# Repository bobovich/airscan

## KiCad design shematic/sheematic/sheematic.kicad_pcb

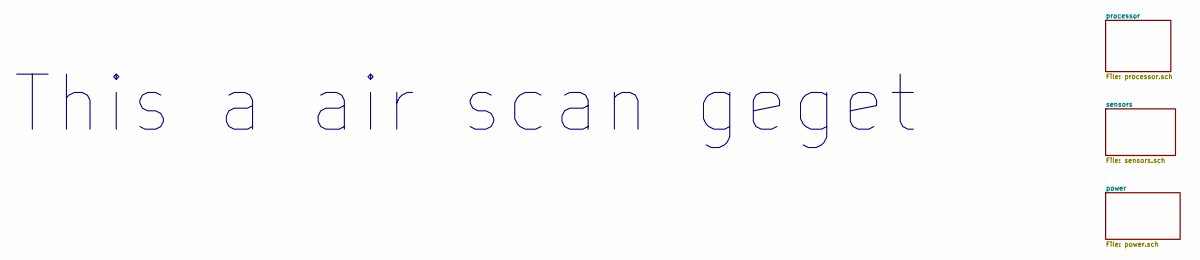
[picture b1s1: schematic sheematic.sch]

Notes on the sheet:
This a air scan geget

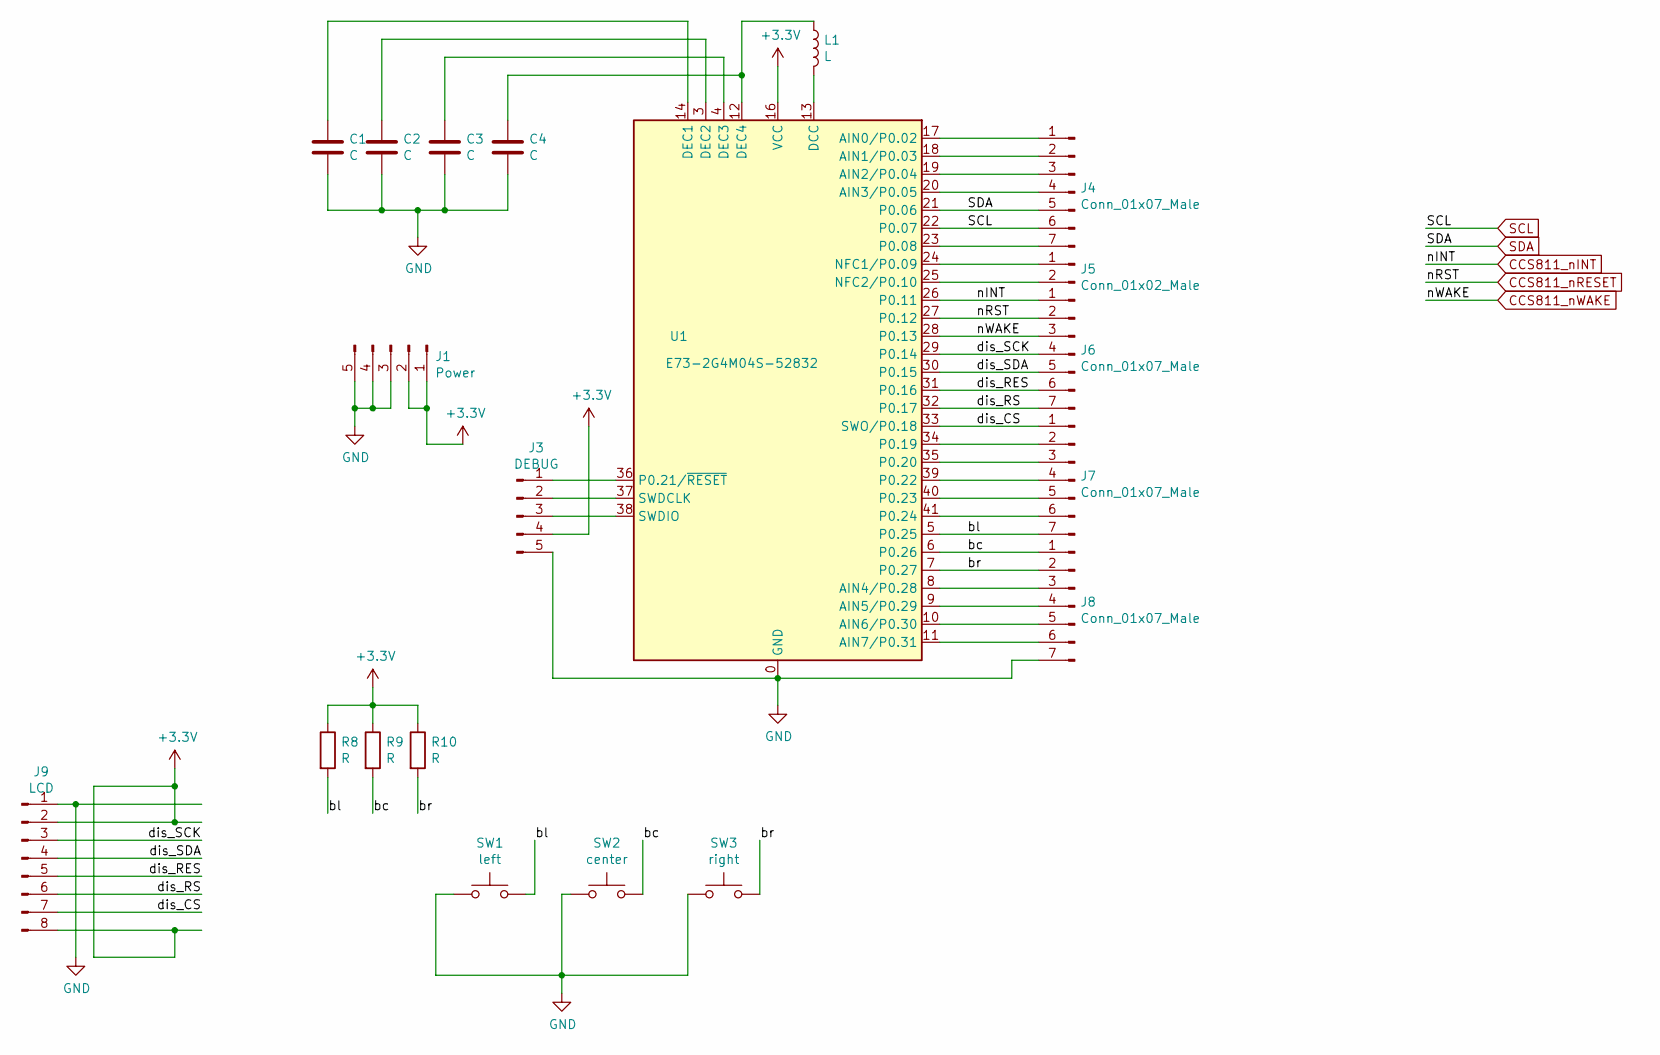
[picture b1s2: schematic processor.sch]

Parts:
C1, C2, C3, C4: C; C_0603_1608Metric_Pad1.08x0.95mm_HandSolder
J1: Power; PinHeader_1x05_P2.54mm_Vertical
J3: DEBUG; PinHeader_1x05_P2.54mm_Vertical
J4, J6, J7, J8: Conn_01x07_Male; PinHeader_1x07_P2.54mm_Vertical
J5: Conn_01x02_Male; PinHeader_1x02_P2.54mm_Vertical
J9: LCD; PinHeader_1x08_P2.54mm_Vertical
L1: L; L_0805_2012Metric_Pad1.15x1.40mm_HandSolder
R8, R9, R10: R; R_0603_1608Metric_Pad1.05x0.95mm_HandSolder
SW1: left; SW_PUSH_6mm
SW2: center; SW_PUSH_6mm
SW3: right; SW_PUSH_6mm
U1: E73-2G4M04S-52832; E73-2G4M04S

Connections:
+3V3: J1.1, J1.2, J3.4, J9.2, J9.8, R8.1, R9.1, R10.1, U1.16 (VCC); also elsewhere on the board
/processor/bc: J8.1, R9.2, SW2.2, U1.6 (P0.26)
/processor/bl: J7.7, R8.2, SW1.2, U1.5 (P0.25)
/processor/br: J8.2, R10.2, SW3.2, U1.7 (P0.27)
/processor/dis_CS: J7.1, J9.7, U1.33 (SWO/P0.18)
/processor/dis_RES: J6.6, J9.5, U1.31 (P0.16)
/processor/dis_RS: J6.7, J9.6, U1.32 (P0.17)
/processor/dis_SCK: J6.4, J9.3, U1.29 (P0.14)
/processor/dis_SDA: J6.5, J9.4, U1.30 (P0.15)
CCS811_nINT: J6.1, U1.26 (P0.11); also elsewhere on the board
CCS811_nRESET: J6.2, U1.27 (P0.12); also elsewhere on the board
CCS811_nWAKE: J6.3, U1.28 (P0.13); also elsewhere on the board
GND: C1.2, C2.2, C3.2, C4.2, J1.3, J1.4, J1.5, J3.5, J8.7, J9.1, SW1.1, SW2.1, SW3.1, U1.0 (GND), U1.1 (GND), U1.2 (GND), U1.15 (GND), U1.42 (GND), U1.43 (GND); also elsewhere on the board
unnamed: C1.1, U1.14 (DEC1)
unnamed: C2.1, U1.3 (DEC2)
unnamed: C3.1, U1.4 (DEC3)
unnamed: C4.1, L1.1, U1.12 (DEC4)
unnamed: J3.1, U1.36 (P0.21/~RESET)
unnamed: J3.2, U1.37 (SWDCLK)
unnamed: J3.3, U1.38 (SWDIO)
unnamed: J4.1, U1.17 (AIN0/P0.02)
unnamed: J4.2, U1.18 (AIN1/P0.03)
unnamed: J4.3, U1.19 (AIN2/P0.04)
unnamed: J4.4, U1.20 (AIN3/P0.05)
unnamed: J4.7, U1.23 (P0.08)
unnamed: J5.1, U1.24 (NFC1/P0.09)
unnamed: J5.2, U1.25 (NFC2/P0.10)
unnamed: J7.2, U1.34 (P0.19)
unnamed: J7.3, U1.35 (P0.20)
unnamed: J7.4, U1.39 (P0.22)
unnamed: J7.5, U1.40 (P0.23)
unnamed: J7.6, U1.41 (P0.24)
unnamed: J8.3, U1.8 (AIN4/P0.28)
unnamed: J8.4, U1.9 (AIN5/P0.29)
unnamed: J8.5, U1.10 (AIN6/P0.30)
unnamed: J8.6, U1.11 (AIN7/P0.31)
unnamed: L1.2, U1.13 (DCC)
SCL: J4.6, U1.22 (P0.07); also elsewhere on the board
SDA: J4.5, U1.21 (P0.06); also elsewhere on the board

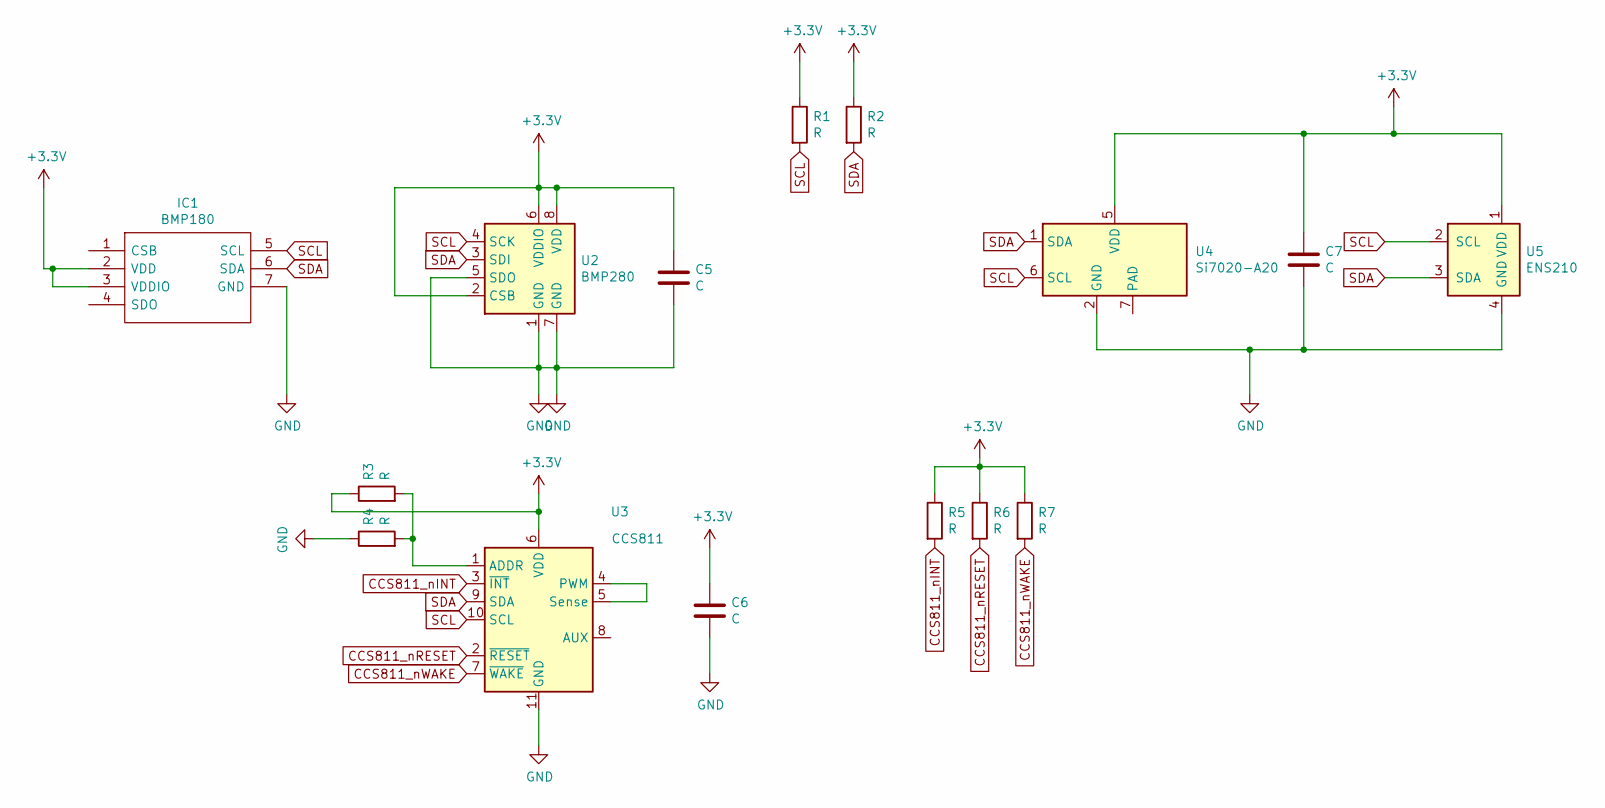
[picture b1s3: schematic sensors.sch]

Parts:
C5, C6, C7: C; C_0603_1608Metric_Pad1.08x0.95mm_HandSolder
IC1: BMP180; Manufacturer_Part_Number BMP180; Mouser Part Number 262-BMP180
R1, R2, R3, R4, R5, R6, R7: R; R_0603_1608Metric_Pad1.05x0.95mm_HandSolder
U2: BMP280; Bosch_LGA-8_2x2.5mm_P0.65mm_ClockwisePinNumbering
U3: CCS811; AMS_LGA-10-1EP_2.7x4mm_P0.6mm
U4: Si7020-A20; DFN-6-1EP_3x3mm_P1mm_EP1.5x2.4mm
U5: ENS210; AMS_QFN-4-1EP_2x2mm_P0.95mm_EP0.7x1.6mm

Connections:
+3V3: C5.1, C6.1, C7.1, IC1.2 (VDD), IC1.3 (VDDIO), R1.1, R2.1, R3.1, R5.1, R6.1, R7.1, U2.2 (CSB), U2.6 (VDDIO), U2.8 (VDD), U3.6 (VDD), U4.5 (VDD), U5.1 (VDD); also elsewhere on the board
CCS811_nINT: R5.2, U3.3 (~INT); also elsewhere on the board
CCS811_nRESET: R6.2, U3.2 (~RESET); also elsewhere on the board
CCS811_nWAKE: R7.2, U3.7 (~WAKE); also elsewhere on the board
GND: C5.2, C6.2, C7.2, IC1.7 (GND), R4.1, U2.1 (GND), U2.5 (SDO), U2.7 (GND), U3.11 (GND), U4.2 (GND), U5.4 (GND), U5.5 (GND); also elsewhere on the board
unnamed: R3.2, R4.2, U3.1 (ADDR)
unnamed: U3.4 (PWM), U3.5 (Sense)
SCL: IC1.5 (SCL), R1.2, U2.4 (SCK), U3.10 (SCL), U4.6 (SCL), U5.2 (SCL); also elsewhere on the board
SDA: IC1.6 (SDA), R2.2, U2.3 (SDI), U3.9 (SDA), U4.1 (SDA), U5.3 (SDA); also elsewhere on the board

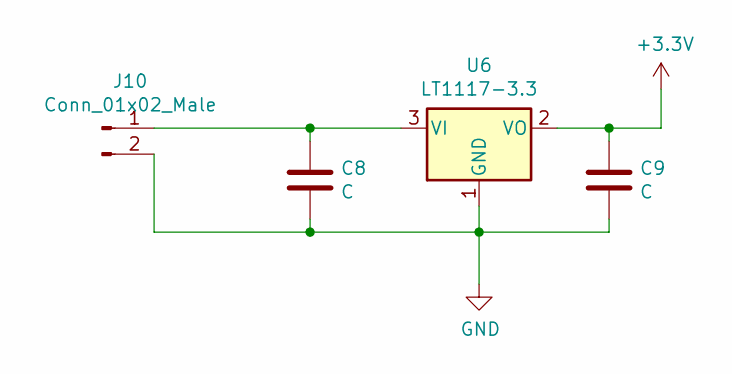
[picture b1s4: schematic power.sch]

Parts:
C8, C9: C; C_0603_1608Metric_Pad1.08x0.95mm_HandSolder
J10: Conn_01x02_Male; PinHeader_1x02_P2.54mm_Vertical
U6: LT1117-3.3; SOT-223-3_TabPin2

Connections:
+3V3: C9.1, U6.2 (VO); also elsewhere on the board
GND: C8.2, C9.2, J10.2, U6.1 (GND); also elsewhere on the board
unnamed: C8.1, J10.1, U6.3 (VI)

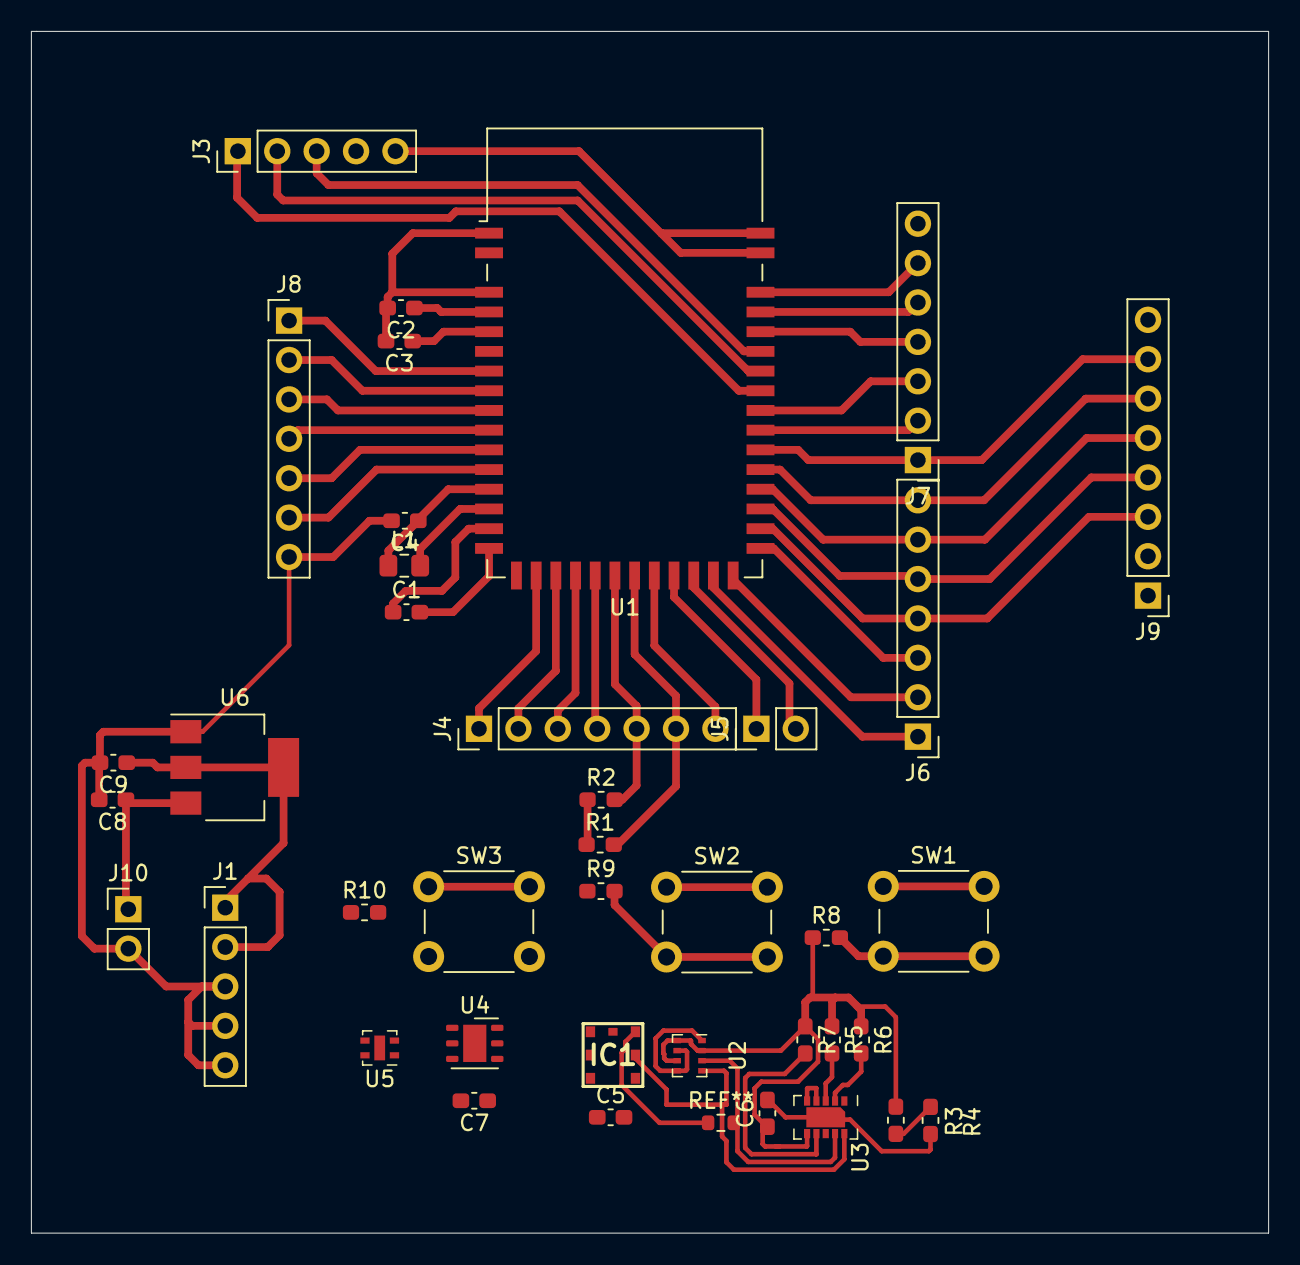
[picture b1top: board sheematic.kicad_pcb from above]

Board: 2 copper layers, 79.8 x 77.5 mm, 39 parts (0 on the bottom side), 42 nets.

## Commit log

2021-02-14 init
2021-02-15 cpu updated
2021-02-20 modify for warios drive
